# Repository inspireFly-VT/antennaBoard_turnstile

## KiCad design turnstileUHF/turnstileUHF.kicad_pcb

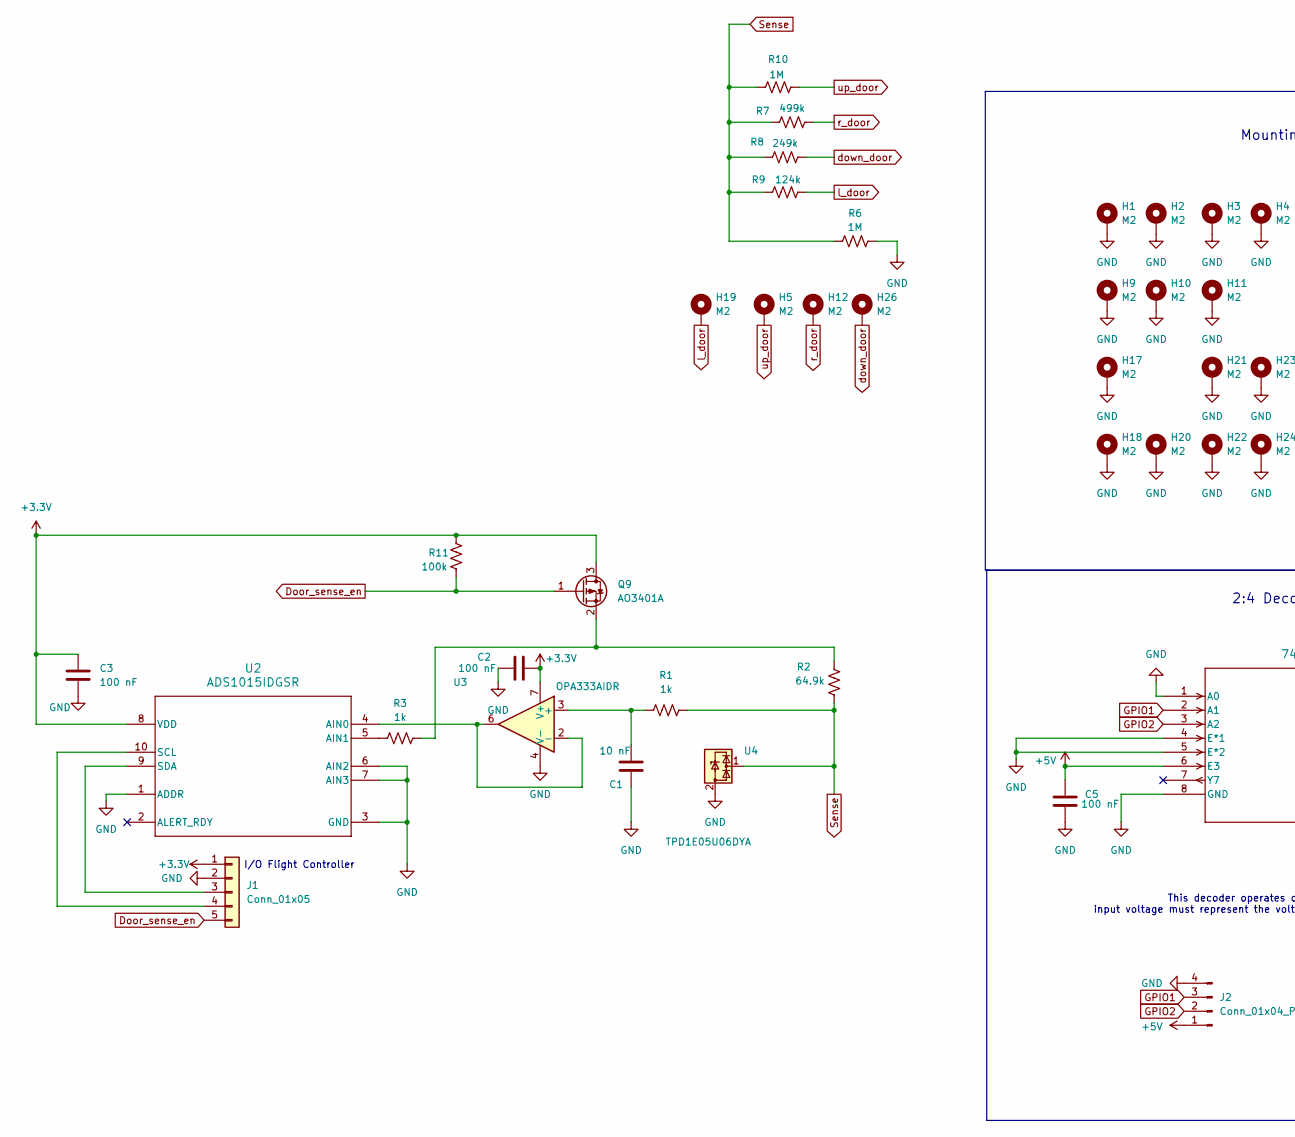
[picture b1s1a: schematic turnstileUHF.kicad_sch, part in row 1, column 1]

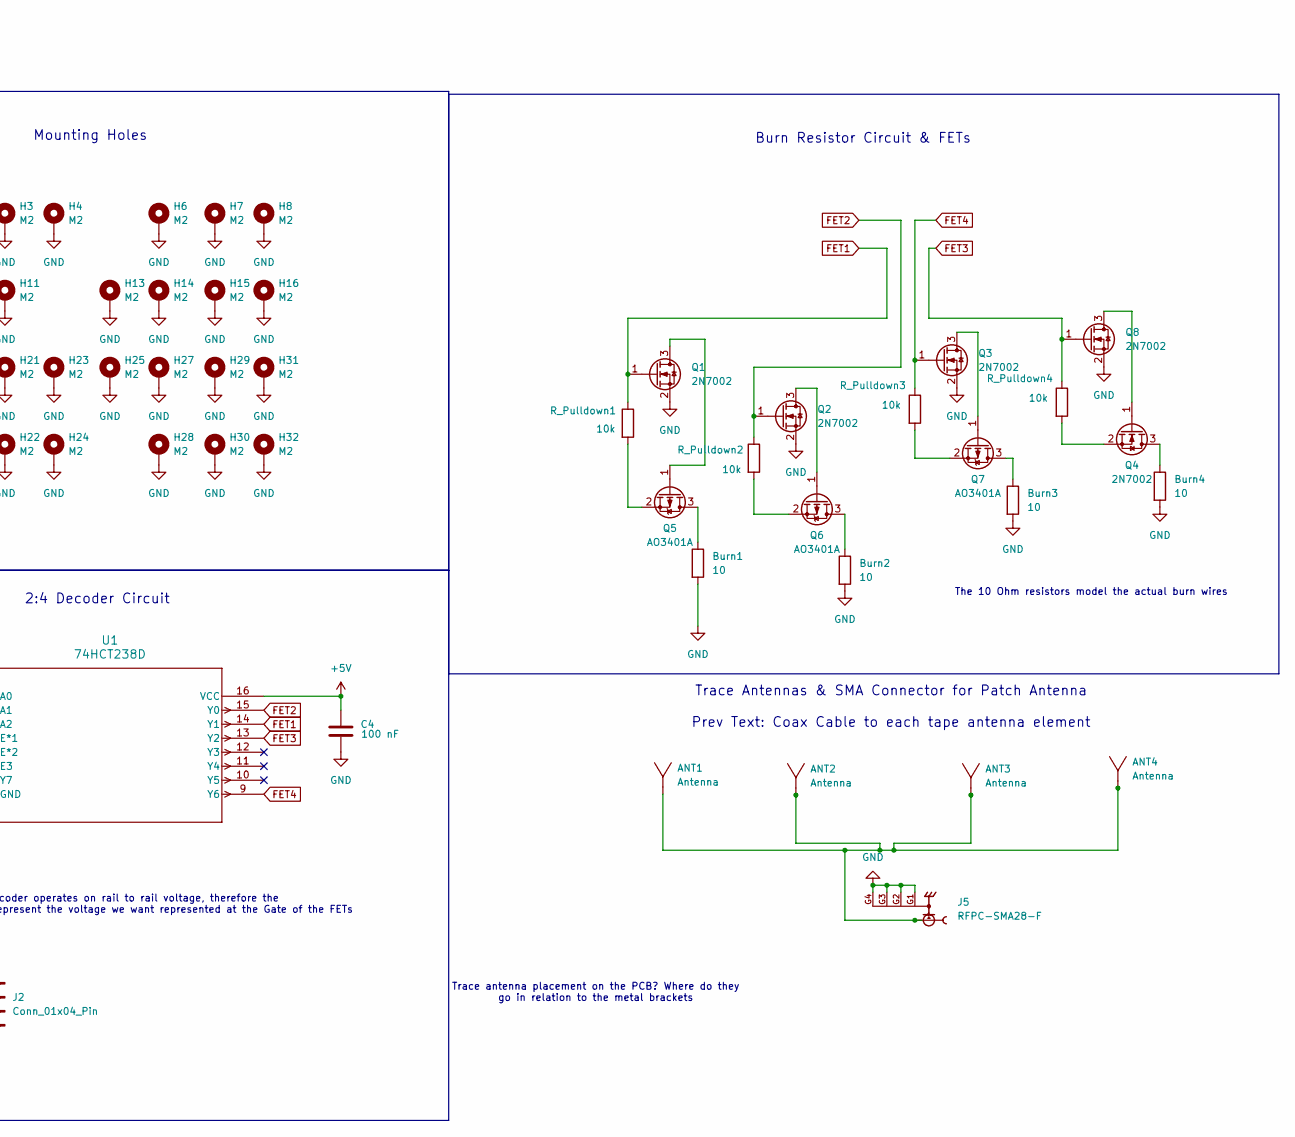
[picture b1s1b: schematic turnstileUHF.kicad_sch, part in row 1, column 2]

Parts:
ANT1, ANT2, ANT3, ANT4: Antenna; Antenna_Tape_pad
Burn1, Burn2, Burn3, Burn4: 10; R_2512_6332Metric_Pad1.40x3.35mm_HandSolder
C1: 10 nF; C_0402_1005Metric_Pad0.74x0.62mm_HandSolder
C2, C3, C4, C5: 100 nF; C_0402_1005Metric_Pad0.74x0.62mm_HandSolder
H1, H2, H3, H4, H5, H6, H7, H8, H9, H10, H11, H12, H13, H14, H15, H16, H17, H18, H19, H20, H21, H22, H23, H24, H25, H26, H27, H28, H29, H30, H31, H32: M2; MountingHole_2mm_custom
J1: Conn_01x05; PinSocket_1x05_P2.54mm_Vertical
J2: Conn_01x04_Pin; PinSocket_1x04_P2.54mm_Vertical
J5: RFPC-SMA28-F; GRADCONN_RFPC-SMA28-F; PARTREV 1.0; DigiKey_Part_Number 2073-RFPC-SMA28-F-ND
Q1, Q2, Q3, Q4, Q8: 2N7002; SOT-23
Q5, Q6, Q7, Q9: AO3401A; SOT-23
R1, R3: 1k; R_0402_1005Metric_Pad0.72x0.64mm_HandSolder
R2: 64.9k; R_0402_1005Metric_Pad0.72x0.64mm_HandSolder
R6, R10: 1M; R_0402_1005Metric_Pad0.72x0.64mm_HandSolder
R7: 499k; R_0402_1005Metric_Pad0.72x0.64mm_HandSolder
R8: 249k; R_0402_1005Metric_Pad0.72x0.64mm_HandSolder
R9: 124k; R_0402_1005Metric_Pad0.72x0.64mm_HandSolder
R11: 100k; R_0402_1005Metric_Pad0.72x0.64mm_HandSolder
R_Pulldown1, R_Pulldown2, R_Pulldown3, R_Pulldown4: 10k; R_0402_1005Metric_Pad0.72x0.64mm_HandSolder
U1: 74HCT238D; SOT109-1_NXP
U2: ADS1015IDGSR; SOP50P490X110-10N; MPN ADS1015IDGSR
U3: OPA333AIDR; D8
U4: TPD1E05U06DYA; D_SOD-523

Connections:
+3.3V: C2.2, C3.1, J1.1, Q9.3 (D), R11.2, U2.8 (VDD), U3.7 (V+)
+5V: C4.2, C5.2, J2.1, U1.6 (E3), U1.16 (VCC)
Door_sense_en: J1.5, Q9.1 (G), R11.1
FET1: Q1.1 (G), R_Pulldown1.1, U1.14 (Y1)
FET2: Q2.1 (G), R_Pulldown2.1, U1.15 (Y0)
FET3: Q8.1 (G), R_Pulldown4.1, U1.13 (Y2)
FET4: Q3.1 (G), R_Pulldown3.1, U1.9 (Y6)
GND: Burn1.2, Burn2.2, Burn3.2, Burn4.2, C1.2, C2.1, C3.2, C4.1, C5.1, H1.1 (1_1), H2.1 (1_1), H3.1 (1_1), H4.1 (1_1), H6.1 (1_1), H7.1 (1_1), H8.1 (1_1), H9.1 (1_1), H10.1 (1_1), H11.1 (1_1), H13.1 (1_1), H14.1 (1_1), H15.1 (1_1), H16.1 (1_1), H17.1 (1_1), H18.1 (1_1), H20.1 (1_1), H21.1 (1_1), H22.1 (1_1), H23.1 (1_1), H24.1 (1_1), H25.1 (1_1), H27.1 (1_1), H28.1 (1_1), H29.1 (1_1), H30.1 (1_1), H31.1 (1_1), H32.1 (1_1), J1.2, J2.4, J5.G1, J5.G2, J5.G3, J5.G4, Q1.2 (S), Q2.2 (S), Q3.2 (S), Q8.2 (S), R6.2, U1.1 (A0), U1.4 (E*1), U1.5 (E*2), U1.8 (GND), U2.1 (ADDR), U2.3 (GND), U2.6 (AIN2), U2.7 (AIN3), U3.4 (V-), U4.2 (GND)
GPIO1: J2.3, U1.2 (A1)
GPIO2: J2.2, U1.3 (A2)
unnamed: ANT1.1 (~_1), ANT2.1 (~_1), ANT3.1 (~_1), ANT4.1 (~_1), J5.1
unnamed: J1.3, U2.9 (SDA)
unnamed: J1.4, U2.10 (SCL)
unnamed: Q1.3 (D), Q5.1 (G)
unnamed: Q2.3 (D), Q6.1 (G)
unnamed: Q3.3 (D), Q7.1 (G)
unnamed: Burn4.1, Q4.3 (D)
unnamed: Q4.1 (G), Q8.3 (D)
unnamed: Q4.2 (S), R_Pulldown4.2
unnamed: Burn1.1, Q5.3 (D)
unnamed: Q5.2 (S), R_Pulldown1.2
unnamed: Burn2.1, Q6.3 (D)
unnamed: Q6.2 (S), R_Pulldown2.2
unnamed: Burn3.1, Q7.3 (D)
unnamed: Q7.2 (S), R_Pulldown3.2
unnamed: Q9.2 (S), R2.1, R3.2
unnamed: U2.4 (AIN0), U3.2 (-), U3.6
unnamed: R3.1, U2.5 (AIN1)
unnamed: C1.1, R1.2, U3.3 (+)
Sense: R1.1, R2.2, R6.1, R7.1, R8.1, R9.1, R10.1, U4.1 (I/O)
down_door: H26.1 (1_1), R8.2
l_door: H19.1 (1_1), R9.2
r_door: H12.1 (1_1), R7.2
up_door: H5.1 (1_1), R10.2

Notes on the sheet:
This decoder operates on rail to rail voltage, therefore the input voltage must represent the voltage we want represented at the Gate of the FETs
The 10 Ohm resistors model the actual burn wires
Mounting Holes
Trace Antennas & SMA Connector for Patch Antenna Prev Text: Coax Cable to each tape antenna element
Burn Resistor Circuit & FETs
Trace antenna placement on the PCB? Where do they go in relation to the metal brackets
I/O Flight Controller
2:4 Decoder Circuit

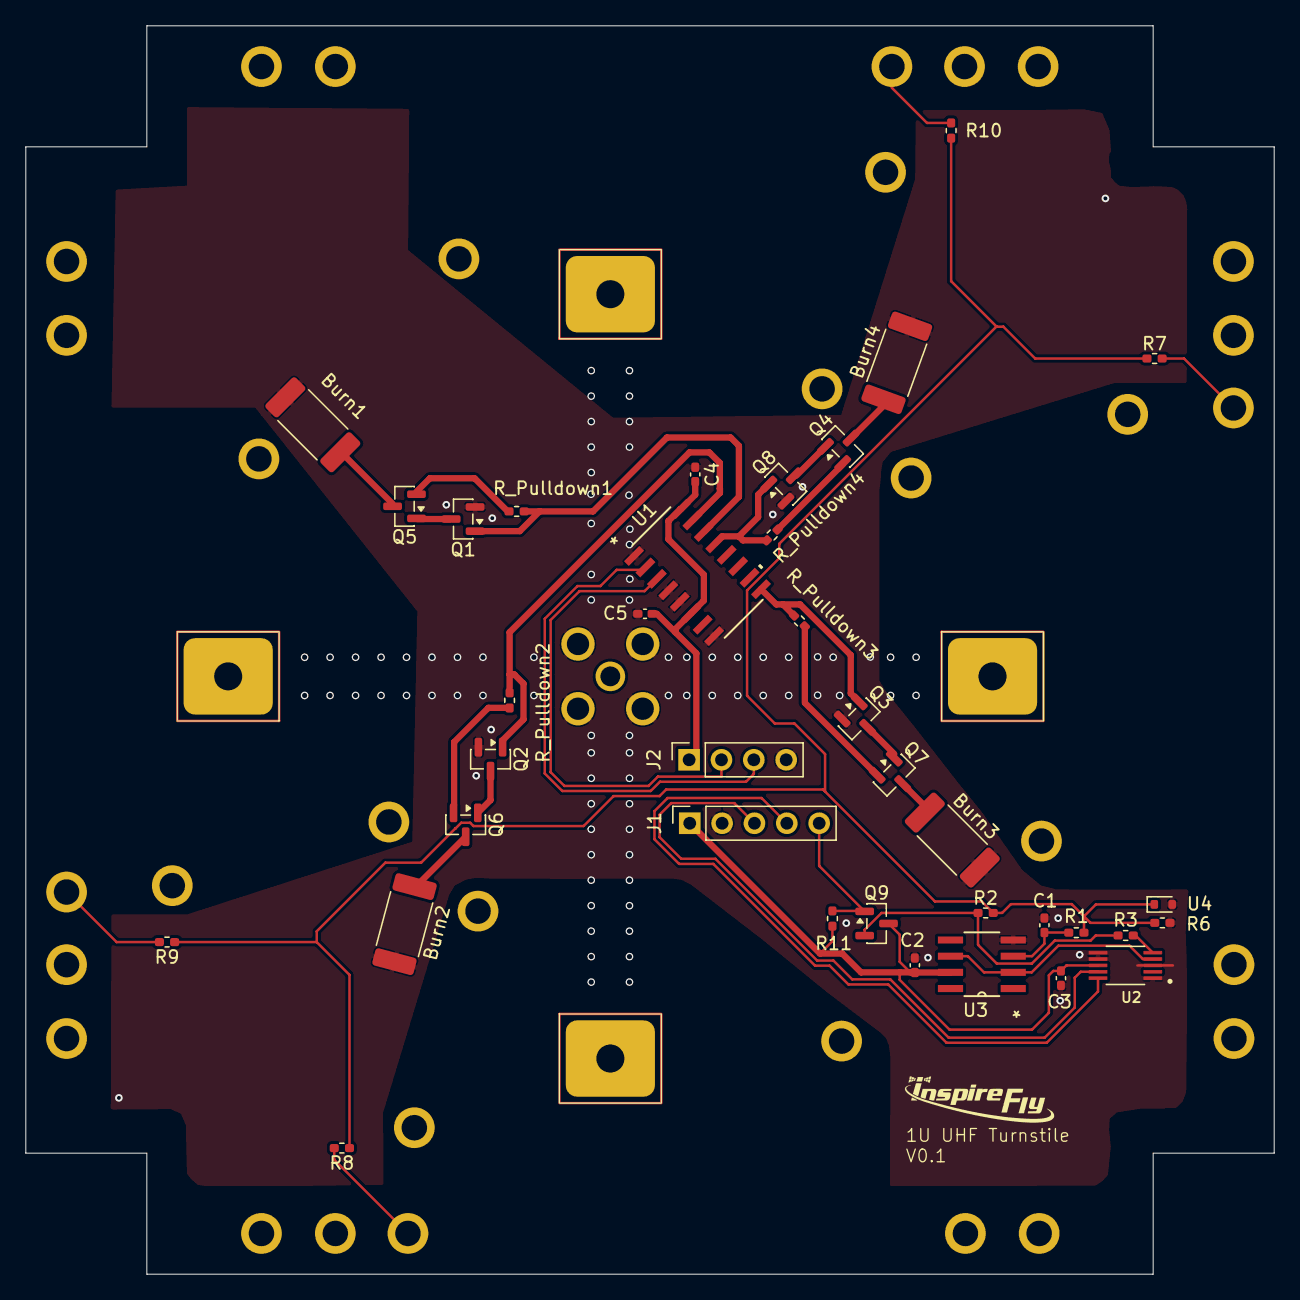
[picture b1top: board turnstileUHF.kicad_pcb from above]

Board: 4 copper layers, 98.0 x 98.0 mm, 74 parts (1 on the bottom side), 34 nets.

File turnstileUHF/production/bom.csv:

Designator,Footprint,Quantity,Value,LCSC Part #
"ANT1, ANT2, ANT3, ANT4",Antenna_Tape_pad,4,Antenna,
"BURN1, BURN2, BURN3, BURN4",2512,4,10,
C1,0402,1,10 nF,
"C2, C3, C4, C5",0402,4,100 nF,
J1,PinSocket_1x05_P2.54mm_Vertical,1,Conn_01x05,
J2,PinSocket_1x04_P2.54mm_Vertical,1,Conn_01x04_Pin,
J5,GRADCONN_RFPC-SMA28-F,1,RFPC-SMA28-F,
"Q1, Q2, Q3, Q4, Q8",SOT-23,5,2N7002,
"Q5, Q6, Q7, Q9",SOT-23,4,AO3401A,
"R1, R3",0402,2,1k,
"R10, R6",0402,2,1M,
R11,0402,1,100k,
R2,0402,1,64.9k,
R7,0402,1,499k,
R8,0402,1,249k,
R9,0402,1,124k,
"R_PULLDOWN1, R_PULLDOWN2, R_PULLDOWN3, R_PULLDOWN4",0402,4,10k,
U1,SOT109-1_NXP,1,74HCT238D,
U2,SOP50P490X110-10N,1,ADS1015IDGSR,ADS1015IDGSR
U3,D8,1,OPA333AIDR,
U4,D_SOD-523,1,TPD1E05U06DYA,

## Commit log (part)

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2026-02-26 Push Lock
2026-03-03 First round of board sizes
2026-03-03 Pushing last second mounting location changes
2026-03-04 Moved one hole
2026-03-06 Test burn resistors placed
2026-04-08 burn wire circuit
2026-04-21 burn wire routing
